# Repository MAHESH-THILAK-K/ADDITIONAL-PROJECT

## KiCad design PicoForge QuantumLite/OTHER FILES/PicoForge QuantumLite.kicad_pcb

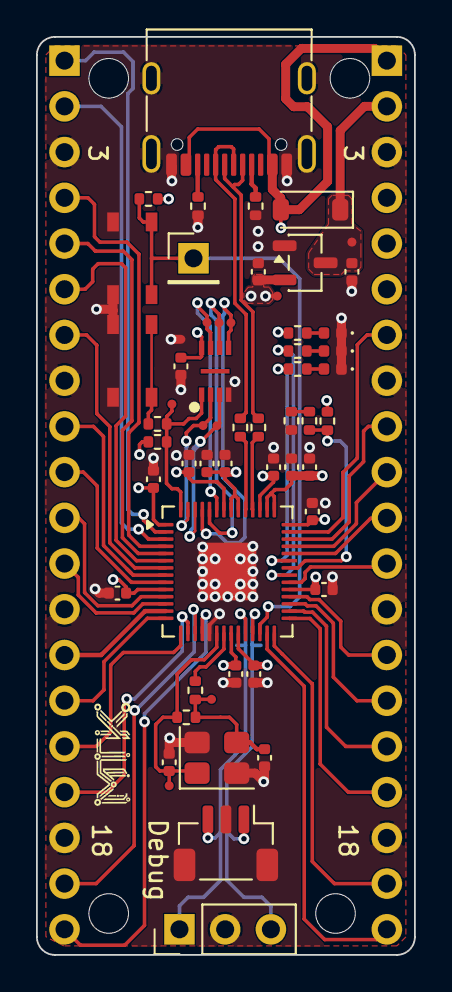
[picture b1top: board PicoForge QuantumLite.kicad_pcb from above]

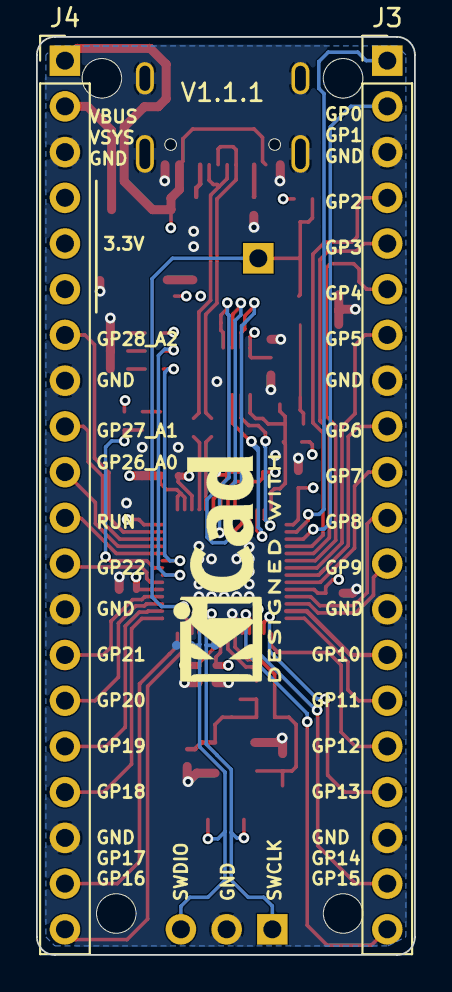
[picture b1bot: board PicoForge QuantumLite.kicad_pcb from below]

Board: 4 copper layers, 21.0 x 51.0 mm, 65 parts (5 on the bottom side), 58 nets.

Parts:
C1, C2, C5, C6, C7, C8, C9, C10, C11, C12, C15: 100nF; C_0402_1005Metric
C3, C4, C13, C14: 1uF; C_0402_1005Metric
C16, C17: 27p; C_0402_1005Metric
D1: D_Schottky; D_SOD-123
D2, D3, D4: LED; LED_0402_1005Metric
H1, H2, H3, H4: MountingHole; MountingHole_2.2mm_M2
J1: USB_C_Receptacle_USB2.0; USB_C_Receptacle_G-Switch_GT-USB-7010ASV
J3, J4: Conn_01x20; PinHeader_1x20_P2.54mm_Vertical
J5: Conn_01x03; PinHeader_1x03_P2.54mm_Vertical
J6: Conn_01x03_MountingPin; JST_SH_BM03B-SRSS-TB_1x03-1MP_P1.00mm_Vertical
J7: Conn_01x01_Pin; PinHeader_1x01_P2.54mm_Vertical
R1, R2, R3, R6, R7: 5.1k; R_0402_1005Metric
R4, R5: 27R; R_0402_1005Metric
R8, R9, R10, R11, R12, R13, R14, R15: 1k; R_0402_1005Metric
SW1, SW2: SW_Push; ALPSALPINE_SKRPACE010
TP1, TP2, TP3, TP4, TP5, TP6, TP7, TP8, TP9, TP10, TP11, TP12, TP13: TestPoint_pad
U1: XC6206P332MR; SOT-23-3
U2: RP2040; QFN-56-1EP_7x7mm_P0.4mm_EP3.2x3.2mm
U3: W25Q16JVUXIQ
Y1: 12MHz; Crystal_SMD_3225-4Pin_3.2x2.5mm

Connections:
+1V1: C1.1, C2.1, C3.1, U2.23 (DVDD), U2.45 (VREG_VOUT), U2.50 (DVDD)
+3.3V: C4.1, C5.1, C6.1, C7.1, C8.1, C9.1, C10.1, C11.1, C12.1, C14.1, C15.1, J4.4, J4.5, J4.6, R10.1, R11.1, R12.1, TP2.1 (1_1), U1.2 (VO), U2.1 (IOVDD), U2.10 (IOVDD), U2.22 (IOVDD), U2.33 (IOVDD), U2.42 (IOVDD), U2.43 (ADC_AVDD), U2.44 (VREG_IN), U2.48 (USB_VDD), U2.49 (IOVDD), U3.8 (VCC)
/CC1: J1.A5 (CC1), R1.1
/CC2: J1.B5 (CC2), R2.1
/GPIO0: J3.1, U2.2 (GPIO0)
/GPIO1: J3.2, U2.3 (GPIO1)
/GPIO2: J3.4, U2.4 (GPIO2)
/GPIO3: J3.5, U2.5 (GPIO3)
/GPIO4: J3.6, U2.6 (GPIO4)
/GPIO5: J3.7, U2.7 (GPIO5)
/GPIO6: J3.9, U2.8 (GPIO6)
/GPIO7: J3.10, U2.9 (GPIO7)
/GPIO8: J3.11, U2.11 (GPIO8)
/GPIO9: J3.12, U2.12 (GPIO9)
/GPIO10: J3.14, U2.13 (GPIO10)
/GPIO11: J3.15, U2.14 (GPIO11)
/GPIO12: J3.16, U2.15 (GPIO12)
/GPIO13: J3.17, U2.16 (GPIO13)
/GPIO14: J3.19, U2.17 (GPIO14)
/GPIO15: J3.20, U2.18 (GPIO15)
/GPIO16: J4.20, U2.27 (GPIO16)
/GPIO17: J4.19, U2.28 (GPIO17)
/GPIO18: J4.17, U2.29 (GPIO18)
/GPIO19: J4.16, U2.30 (GPIO19)
/GPIO20: J4.15, U2.31 (GPIO20)
/GPIO21: J4.14, U2.32 (GPIO21)
/GPIO22: J4.12, U2.34 (GPIO22)
/GPIO23: R13.1, U2.35 (GPIO23)
/GPIO24: R3.1, R6.2, U2.36 (GPIO24)
/GPIO25: R14.1, U2.37 (GPIO25)
/GPIO26_ADC0: J4.11, U2.38 (GPIO26_ADC0)
/GPIO27_ADC1: J4.10, U2.39 (GPIO27_ADC1)
/GPIO28_ADC2: J4.9, U2.40 (GPIO28_ADC2)
/GPIO29_ADC3: J4.7, U2.41 (GPIO29_ADC3)
/LED_3V3: D2.2 (A), R12.2
/LED_BUILT_IN1: D4.2 (A), R14.2
/LED_BUILT_IN2: D3.2 (A), R13.2
/QSPI_SCLK: TP9.1 (1_1), U2.52 (QSPI_SCLK), U3.6 (CLK)
/QSPI_SD0: TP10.1 (1_1), U2.53 (QSPI_SD0), U3.5 (DI(IO0))
/QSPI_SD1: TP11.1 (1_1), U2.55 (QSPI_SD1), U3.2 (DO(IO1))
/QSPI_SD2: TP12.1 (1_1), U2.54 (QSPI_SD2), U3.3 (IO2)
/QSPI_SD3: TP13.1 (1_1), U2.51 (QSPI_SD3), U3.7 (IO3)
/QSPI_SS: R10.2, R15.1, TP8.1 (1_1), U2.56 (QSPI_SS), U3.1 (~CS)
/RDIV: R6.1, R7.2
/RUN: J7.1 (Pin_1_1), R11.2, SW2.2, U2.26 (RUN)
/SW1_{PULL-UP}: R15.2, SW1.2
/SWCLK: J5.1, J6.3, TP5.1 (1_1), U2.24 (SWCLK)
/SWD: J5.3, J6.1, TP6.1 (1_1), U2.25 (SWD)
/USB_DN: J1.A7 (D-), J1.B7 (D-), R5.1
/USB_DP: J1.A6 (D+), J1.B6 (D+), R4.1
/USB_R_DN: R5.2, U2.46 (USB_DM)
/USB_R_DP: R4.2, U2.47 (USB_DP)
/Xin: C16.1, R8.1, TP3.1 (1_1), U2.20 (XIN), Y1.1
/Xout: R9.2, U2.21 (XOUT)
/XoutR: C17.1, R8.2, R9.1, TP4.1 (1_1), Y1.3
GND: C1.2, C2.2, C3.2, C4.2, C5.2, C6.2, C7.2, C8.2, C9.2, C10.2, C11.2, C12.2, C13.2, C14.2, C15.2, C16.2, C17.2, D2.1 (K), D3.1 (K), D4.1 (K), J1.A1 (GND), J1.A12 (GND), J1.B1 (GND), J1.B12 (GND), J1.SH (SHIELD), J3.3, J3.8, J3.13, J3.18, J4.3, J4.8, J4.13, J4.18, J5.2, J6.2, J6.MP (MountPin), R1.2, R2.2, R7.1, SW1.1, SW2.1, TP7.1 (1_1), U1.1 (GND), U2.19 (TESTEN), U2.57 (GND), U3.4 (GND), Y1.2, Y1.4
VBUS: D1.2 (A), J1.A4 (VBUS), J1.A9 (VBUS), J1.B4 (VBUS), J1.B9 (VBUS), J4.1, R3.2
VCC: C13.1, D1.1 (K), J4.2, TP1.1 (1_1), U1.3 (VI)

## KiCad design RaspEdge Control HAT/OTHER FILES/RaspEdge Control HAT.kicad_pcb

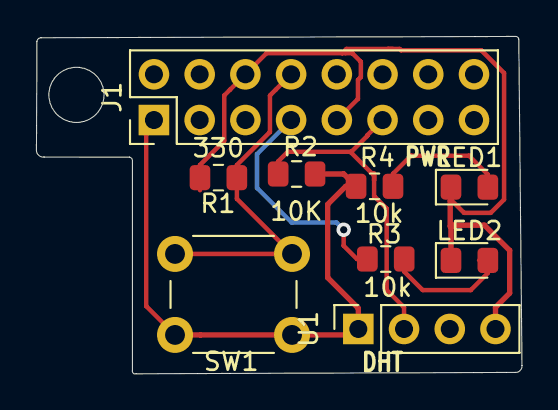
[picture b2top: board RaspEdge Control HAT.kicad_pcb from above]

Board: 2 copper layers, 27.0 x 18.7 mm, 9 parts (0 on the bottom side), 7 nets.

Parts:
J1: Raspberry_Pi_2_3; PinHeader_2x08_P2.54mm_Vertical
LED1, LED2: LED; LED_0805_2012Metric_Pad1.15x1.40mm_HandSolder
R1: 330; R_0805_2012Metric_Pad1.15x1.40mm_HandSolder
R2: 10K; R_0805_2012Metric_Pad1.15x1.40mm_HandSolder
R3, R4: 10k; R_0805_2012Metric_Pad1.15x1.40mm_HandSolder
SW1: SW_DPST; SW_PUSH_6mm_H8mm
U1: DHT22; PinSocket_1x04_P2.54mm_Vertical

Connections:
/3V3: J1.1, R2.2, R4.2, SW1.1, U1.1
/button_input: J1.8, R1.1, SW1.2
GND: J1.6, J1.9, LED1.1, LED2.1, R1.2, U1.4
unnamed: LED2.2, R3.1
unnamed: LED1.2, R4.1
unnamed: J1.7, R3.2
unnamed: J1.11, R2.1, U1.2

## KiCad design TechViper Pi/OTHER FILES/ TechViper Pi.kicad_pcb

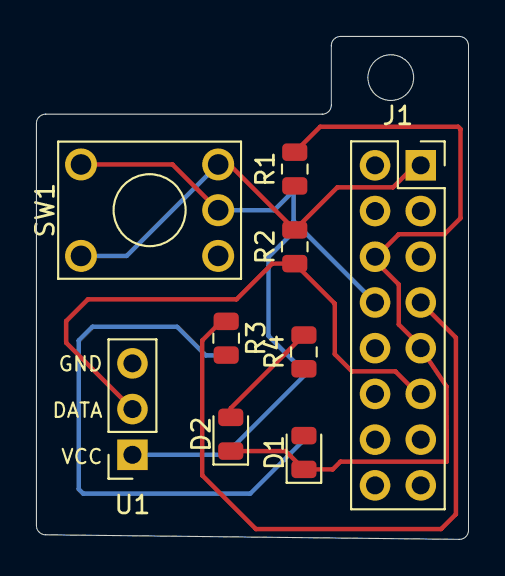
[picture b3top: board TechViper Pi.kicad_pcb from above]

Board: 2 copper layers, 24.0 x 27.9 mm, 9 parts (0 on the bottom side), 7 nets.

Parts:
D1, D2: LED; LED_0805_2012Metric
J1: Raspberry_Pi_2_3; PinSocket_2x08_P2.54mm_Vertical
R1: 10k; R_0805_2012Metric
R2: 330k; R_0805_2012Metric
R3, R4: R; R_0805_2012Metric
SW1: SW_DPST; KSA_Tactile_SPST
U1: DHT22; PinSocket_1x03_P2.54mm_Vertical

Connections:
/3V3: J1.1, R2.2, R4.1, SW1.1, SW1.3, U1.1
/button_input: J1.8, R1.1, SW1.2, SW1.4
GND: D1.1, D2.1, J1.6, J1.9, R1.2
unnamed: D1.2, R3.2
unnamed: D2.2, R4.2
unnamed: J1.7, R3.1
unnamed: J1.11, R2.1, U1.2

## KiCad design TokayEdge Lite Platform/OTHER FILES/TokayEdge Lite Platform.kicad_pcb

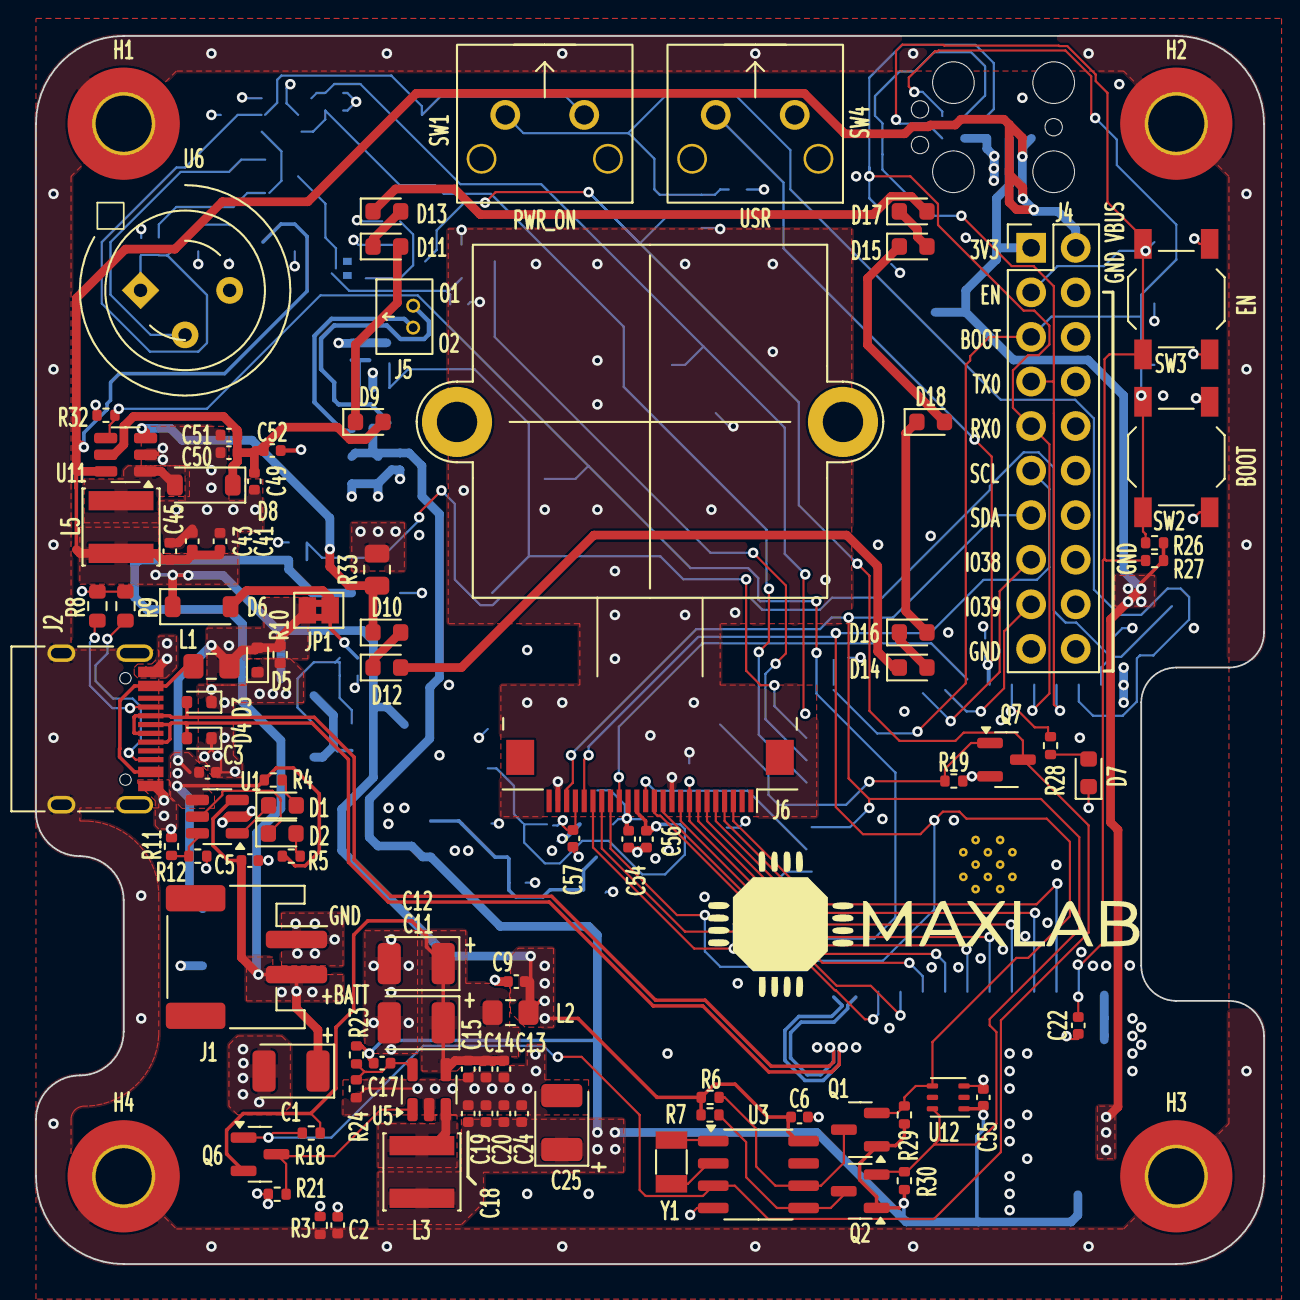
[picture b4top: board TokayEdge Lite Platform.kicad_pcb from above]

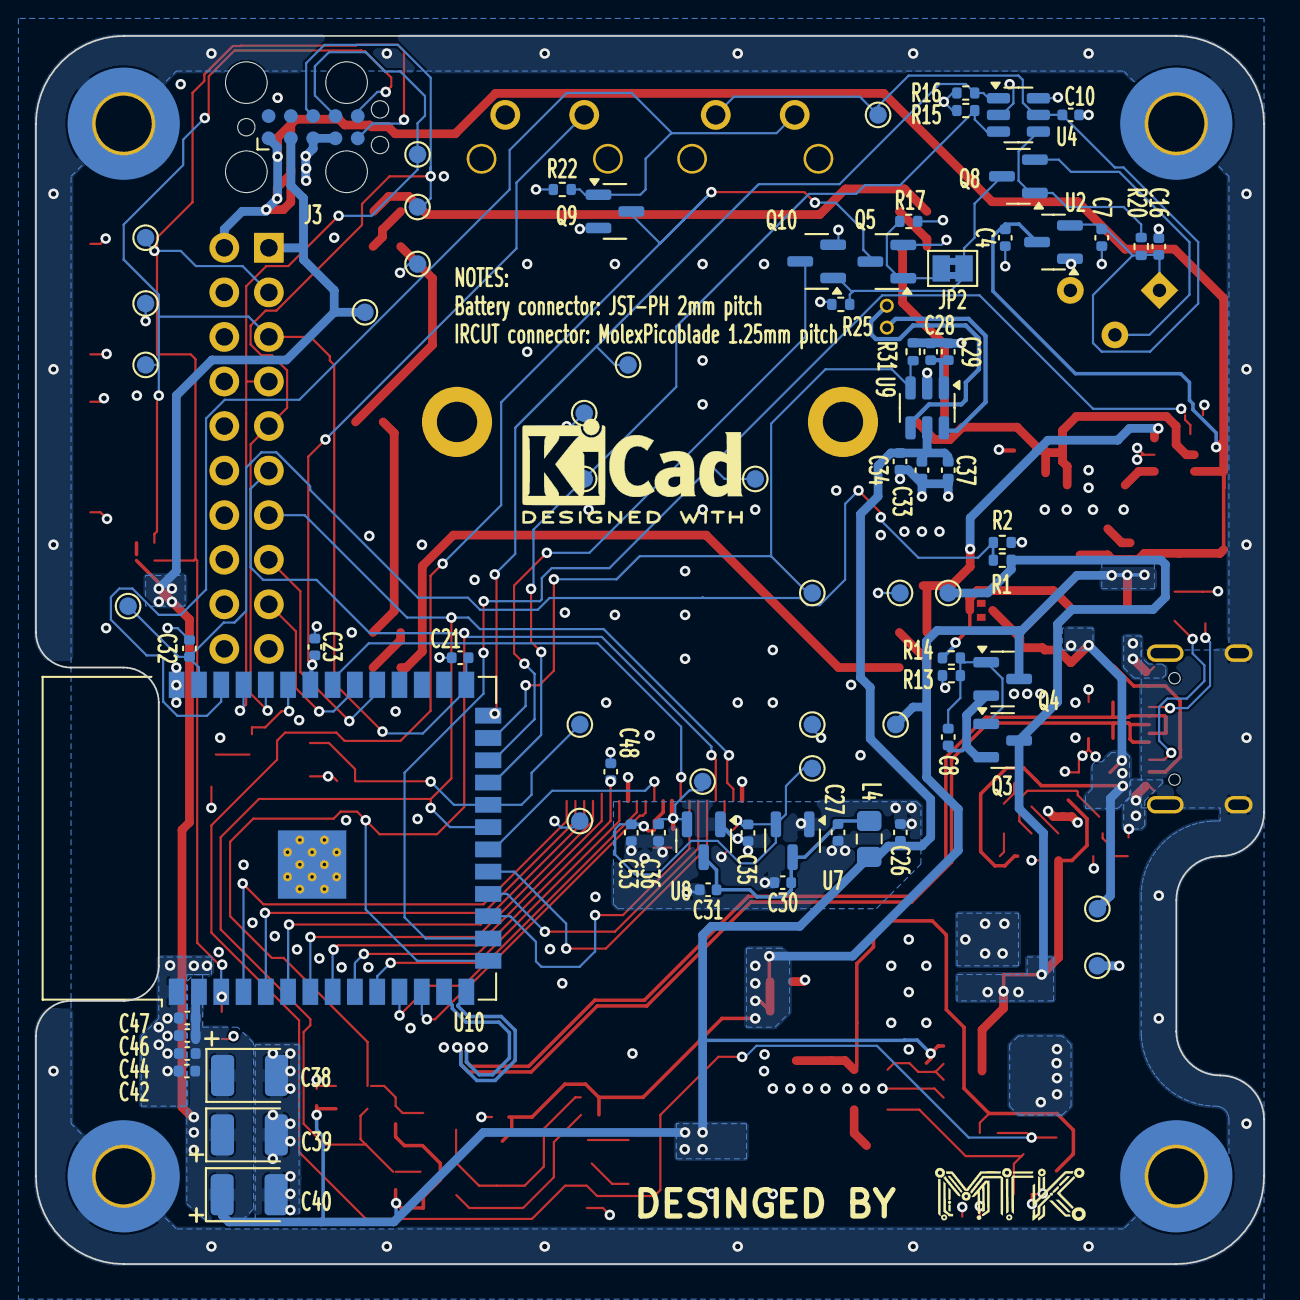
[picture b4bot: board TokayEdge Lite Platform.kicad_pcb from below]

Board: 4 copper layers, 70.0 x 70.0 mm, 176 parts (78 on the bottom side), 84 nets.

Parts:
C1, C11, C12, C25, C38, C39, C40: 100u_CASE-B-3528_TAJB107K006RNJ; CP_EIA-3528-15_AVX-H
C2, C3, C4, C5, C6, C7, C8, C9, C10, C13, C14, C15, C16, C18, C19, C20, C21, C22, C23, C24, C26, C27, C28, C29, C30, C31, C32, C33, C34, C35, C36, C37, C41, C42, C43, C44, C45, C46, C47, C49, C50, C51, C52, C53, C54, C55, C56, C57: 10u_0402_CL05A105KA5NQNC; C_0402_1005Metric
C17, C48: 22p_0402_0402CG220J500NT; C_0402_1005Metric
D1, D7: 0603_RED_KT-0603R; LED_0603_1608Metric
D2: 0603_GREEN_19-217/GHC-YR1S2/3T; LED_0603_1608Metric
D3, D4, D5: SOD-523_BSD5C051L; D_SOD-523
D6, D8: B5819W-SL_SOD-123; D_SOD-123
D9, D10, D11, D12, D13, D14, D15, D16, D17, D18: 0603_IR_850nm_E6C0603IRAC1UDA; LED_0603_1608Metric
H1, H2, H3, H4: MountingHole_Pad; MountingHole_3.2mm_M3_Pad_TopBottom
J1: Conn-01x02_P2mm_NONAME_JST-PH_C47647; JST_PH_S2B-PH-SM4-TB_1x02-1MP_P2.00mm_Horizontal
J2: TYPE-C-31-M-12; USB_C_Receptacle_HRO_TYPE-C-31-M-12
J3: MAXLAB; Tag-Connect_TC2050-IDC-FP_2x05_P1.27mm_Vertical
J4: Conn-02x10_P2.54mm_B-2100S20P-B110; PinHeader_2x10_P2.54mm_Vertical
J5: Conn-01x02_P1.25mm_10114829-10102LF; 10114829-10102LF
J6: Conn_01x24_FFC_0.5mm_AFC01-S24FCC-00; Jushuo_AFC01-S24FCC-00_1x24-1MP_P0.50_Horizontal
JP1: USB_PWR; SolderJumper-2_P1.3mm_Bridged2Bar_Pad1.0x1.5mm
JP2: PIR; SolderJumper-2_P1.3mm_Bridged2Bar_Pad1.0x1.5mm
L1, L2, L4: FB_2A_0805_220R@100MHz_BLM21PG221SN1D; L_0805_2012Metric_Pad1.15x1.40mm_HandSolder
L3, L5: 10u_1.5A_4x4mm_SWPA4030S100MT; L_Sunlord_SWPA40xxS
Q1, Q2, Q5, Q7, Q9, Q10: 2N7002; SOT-23
Q3, Q4, Q6, Q8: AO3401A; SOT-23
R1, R2, R23: 976k_0402_0402WGD9763TCE; R_0402_1005Metric
R3, R13, R15, R16, R17, R18, R19, R21, R22, R24, R25, R31, R32: 215k_0402_0402WGD2153TCE; R_0402_1005Metric
R4, R5, R28: 1k_0402_0402WGF1001TCE; R_0402_1005Metric
R6, R7, R10, R11, R12, R14, R20, R26, R27, R29, R30: 10k_0402_0402WGF1002TCE; R_0402_1005Metric
R8, R9: 5.1k_0603_0603WAF5101T5E; R_0603_1608Metric
R33: 2.43R_0805_0805W8F243KT5E; R_0805_2012Metric
SW1, SW4: SW_PB_90deg_K2-1102AQ-H4CW-01
SW2, SW3: SW_PB_TS-1187A-B-A-B; SW_SPST_TL3342
TP1, TP2, TP3, TP4, TP5, TP6, TP7, TP8, TP9, TP10, TP11, TP12, TP13, TP14, TP15, TP16, TP17, TP18, TP19, TP20, TP21, TP22, TP23, TP24: TestPoint; TestPoint_Pad_D1.0mm
U1: TP4057-42-SOT26-R; SOT-23-6
U2, U7: XC6206-2.8V; SOT-23
U3: PCF85063AT; SO-8_3.9x4.9mm_P1.27mm
U4: TI_SN74LVC1G373DBVR; SOT-23-6
U5: SY8089AAAC; SOT-23-5
U6: PIR_AS312; AS312
U8: RT9166-12GVL; SOT-23
U9: AP1511B; SOT-23-6
U10: ESP32-S3-WROOM-1-N16R8; ESP32-S3-WROOM-1
U11: MT9284-28J; SOT-23-6
U12: LTR-303ALS-01; Lite-On_LTR-303ALS-01
Y1: 32.768kHz_Q13FC1350000400; Crystal_SMD_3215-2Pin_3.2x1.5mm

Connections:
+1V2: C36.1, C54.2, J6.15, TP16.1, U8.2 (VO)
+2V8: C35.1, C53.1, C56.2, C57.2, J6.14, J6.21, TP18.1, U7.2 (VO)
+3V3: C17.1, C18.2, C19.2, C20.2, C24.2, C25.1, C26.1, C33.2, C34.2, C37.2, C38.1, C39.1, C40.1, C42.1, C44.1, C46.1, C47.1, C55.1, J3.2, J4.1, L3.2, L4.1, Q1.1 (G), Q2.1 (G), R23.1, R26.2, R27.2, R29.1, R30.1, TP22.1, U9.5 (VDD), U10.2 (3V3), U12.1 (VDD)
+5V: C3.2, D5.2 (A2), JP1.2 (B), L1.2, R4.1, R5.1, R10.1, TP23.1, U1.4 (V_{cc})
+BATT: C1.1, C5.1, J1.2, Q3.3 (D), R1.1, TP19.1, U1.3 (BAT)
/BATT_DETECT: C32.1, R1.2, R2.1, TP11.1, U10.39 (GPIO1/TOUCH1/ADC1_CH0)
/CAM.D2: J6.6, U10.7 (GPIO7/TOUCH7/ADC1_CH6)
/CAM.D3: J6.4, U10.5 (GPIO5/TOUCH5/ADC1_CH4)
/CAM.D4: J6.3, U10.4 (GPIO4/TOUCH4/ADC1_CH3)
/CAM.D5: J6.5, U10.6 (GPIO6/TOUCH6/ADC1_CH5)
/CAM.D6: J6.7, U10.8 (GPIO15/U0RTS/ADC2_CH4/XTAL_32K_P)
/CAM.D7: J6.9, U10.10 (GPIO17/U1TXD/ADC2_CH6)
/CAM.D8: J6.11, U10.11 (GPIO18/U1RXD/ADC2_CH7/CLK_OUT3)
/CAM.D9: J6.13, U10.20 (GPIO12/TOUCH12/ADC2_CH1/FSPICLK/FSPIIO6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)
/CAM.HREF: J6.16, U10.33 (MTDO/GPIO40/CLK_OUT2)
/CAM.MCLK: J6.12, U10.12 (GPIO8/TOUCH8/ADC1_CH7/SUBSPICS1)
/CAM.PCLK: C48.1, J6.8, U10.9 (GPIO16/U0CTS/ADC2_CH5/XTAL_32K_NH5)
/CAM.PWDN: J6.17, U10.17 (GPIO9/TOUCH9/ADC1_CH8/FSPIHD/SUBSPIHD)
/CAM.RST: J6.19, U10.19 (GPIO11/TOUCH11/ADC2_CH0/FSPID/FSPIIO5/S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)
/CAM.SCL: J4.11, J6.20, Q1.2 (S), R29.2, U10.15 (GPIO3/TOUCH3/ADC1_CH2), U12.4 (SCL)
/CAM.SDA: J4.13, J6.22, Q2.2 (S), R30.2, U10.21 (GPIO13/TOUCH13/ADC2_CH2/FSPIQ/FSPIIO7/S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), U12.6 (SDA)
/CAM.VSYNC: J6.18, U10.18 (GPIO10/TOUCH10/ADC1_CH9/FSPICS0/FSPIIO4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)
/ESP_BOOT: C21.2, J3.6, J4.5, R26.1, SW2.2, TP2.1, U10.27 (GPIO0/BOOT)
/ESP_EN: C22.2, J3.5, J4.3, R27.1, SW3.2, TP1.1, U10.3 (EN)
/IO38: J4.15, U10.31 (GPIO38/FSPIWP/SUBSPIWP)
/IO39: J4.17, U10.32 (MTCK/GPIO39/CLK_OUT3/SUBSPICS1)
/IRCUT_CTRL: R31.2, TP10.1, U9.3 (FBC), U10.25 (GPIO48/SPICLK_N/SUBSPICLK_N_DIFF)
/IRLED_PWM: R32.2, TP14.1, U10.16 (GPIO46), U11.4 (EN)
/PIR_CTRL_D: R15.2, TP8.1, U4.3 (D), U10.23 (GPIO21)
/PIR_CTRL_LE: R16.2, TP7.1, U4.1 (LE), U10.26 (GPIO45)
/PIR_OUT: Q10.3 (D), U10.24 (GPIO47/SPICLK_P/SUBSPICLK_P_DIFF)
/PWRON_DET: Q9.1 (G), R22.2, SW1.2, U10.38 (GPIO2/TOUCH2/ADC1_CH1)
/PWR_EN: Q7.1 (G), R19.2, TP12.1, U10.22 (GPIO14/TOUCH14/ADC2_CH3/FSPIWP/FSPIDQS/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)
/PWR_PIR: C7.1, C10.1, C16.1, R20.1, SW1.1, TP13.1, U2.2 (VO), U4.5 (VCC), U6.1 (VDD)
/RXD0: J3.8, J4.9, TP5.1, U10.36 (U0RXD/GPIO44/CLK_OUT2)
/TXD0: J3.7, J4.7, TP4.1, U10.37 (U0TXD/GPIO43/CLK_OUT1)
/UD+: D4.2 (A2), J2.A6 (D+), J2.B6 (D+), U10.14 (GPIO20/U1CTS/ADC2_CH9/CLK_OUT1/USB_D+)
/UD-: D3.2 (A2), J2.A7 (D-), J2.B7 (D-), U10.13 (GPIO19/U1RTS/ADC2_CH8/CLK_OUT2/USB_D-)
/USR_BTN: C23.2, SW4.2, U10.34 (MTDI/GPIO41/CLK_OUT1)
/USR_LED: R28.1, U10.35 (MTMS/GPIO42)
GND: C1.2, C2.1, C3.1, C4.1, C5.2, C6.2, C7.2, C9.1, C10.2, C11.2, C12.2, C13.1, C14.2, C15.1, C16.2, C18.1, C19.1, C20.1, C21.1, C22.1, C23.1, C24.1, C25.2, C26.2, C27.2, C28.2, C29.2, C30.2, C31.2, C32.2, C33.1, C34.1, C35.2, C36.2, C37.1, C38.2, C39.2, C40.2, C41.1, C42.2, C43.2, C44.2, C45.1, C46.2, C47.2, C48.2, C49.2, C50.1, C51.1, C52.1, C53.2, C54.1, C55.2, C56.1, C57.1, D3.1 (A1), D4.1 (A1), D5.1 (A1), D7.1 (K), J1.1, J2.A1 (GND), J2.A12 (GND), J2.B1 (GND), J2.B12 (GND), J3.3, J3.4, J4.4, J4.6, J4.8, J4.10, J4.12, J4.14, J4.16, J4.18, J4.19, J4.20, J6.10, J6.23, Q5.2 (S), Q7.2 (S), Q9.2 (S), Q10.2 (S), R2.2, R3.2, R8.2, R9.2, R10.2, R11.2, R12.2, R13.2, R15.1, R16.1, R17.1, R19.1, R21.2, R22.1, R24.2, R25.1, R31.1, R32.1, R33.2, SW2.1, SW3.1, SW4.1, TP3.1, TP6.1, TP9.1, TP15.1, TP17.1, TP20.1, TP24.1, U1.2 (GND), U2.1 (GND), U3.4 (VSS), U4.2 (G), U4.6 (~OE), U5.2 (GND), U6.3 (VSS), U7.1 (GND), U8.1 (GND), U9.2 (GND), U10.1 (GND), U10.40 (GND), U10.41 (GND), U11.2 (GND), U12.3 (GND)
GNDPWR: C2.2, H1.1, H2.1, H3.1, H4.1, J2.S1 (SHIELD), R3.1
unnamed: D1.2 (A), R4.2
unnamed: D1.1 (K), U1.1 (~CHRG)
unnamed: D2.2 (A), R5.2
unnamed: D2.1 (K), U1.5 (~STDBY)
unnamed: D6.2 (A), JP1.1 (A), R14.1
unnamed: D7.2 (A), R28.2
unnamed: D8.2 (A), L5.2, U11.1 (SW)
unnamed: C49.1, C50.2, C51.2, C52.2, D8.1 (K), D9.2 (A), U11.5 (OV)
unnamed: D10.2 (A), D12.1 (K)
unnamed: D10.1 (K), R33.1, U11.3 (FB)
unnamed: D9.1 (K), D11.2 (A)
unnamed: D11.1 (K), D13.2 (A)
unnamed: D12.2 (A), D14.1 (K)
unnamed: D13.1 (K), D15.2 (A)
unnamed: D14.2 (A), D16.1 (K)
unnamed: D15.1 (K), D17.2 (A)
unnamed: D16.2 (A), D18.1 (K)
unnamed: D17.1 (K), D18.2 (A)
unnamed: J2.A5 (CC1), R8.1
unnamed: J2.B5 (CC2), R9.1
unnamed: J2.A4 (VBUS), J2.A9 (VBUS), J2.B4 (VBUS), J2.B9 (VBUS), L1.1
unnamed: J5.1, U9.6 (OUT2)
unnamed: J5.2, U9.4 (OUT1)
unnamed: JP2.1 (A), Q8.3 (D), Q10.1 (G), R25.2
unnamed: JP2.2 (B), Q5.1 (G), R17.2
unnamed: Q1.3 (D), R6.2, U3.6 (SCL)
unnamed: Q2.3 (D), R7.2, U3.5 (SDA)
unnamed: C8.1, Q3.1 (G), Q4.1 (G), R13.1, R14.2
unnamed: C8.2, Q3.2 (S), Q4.2 (S)
unnamed: Q5.3 (D), Q6.1 (G), Q7.3 (D), Q9.3 (D), R18.2, U3.3 (~INT)
unnamed: Q6.3 (D), R21.1, U5.1 (EN)
unnamed: C11.1, C12.1, C13.2, C14.1, C15.2, L2.2, Q6.2 (S), R18.1, U5.4 (IN)
unnamed: Q8.1 (G), R20.2, U4.4 (Q)
unnamed: Q8.2 (S), U6.2 (REL)
unnamed: R11.1, R12.1, U1.6 (PROG)
unnamed: U3.1 (OSCI), Y1.2
unnamed: U3.2 (OSCO), Y1.1
unnamed: C17.2, R23.2, R24.1, U5.5 (FB)
unnamed: L3.1, U5.3 (LX)
unnamed: C27.1, C30.1, C31.1, L4.2, U7.3 (VI), U8.3 (VI)
unnamed: C28.1, C29.1, U9.1 (CE)
VBUS: C4.2, C6.1, C9.2, C41.2, C43.1, C45.2, D6.1 (K), J3.1, J4.2, L2.1, L5.1, Q4.3 (D), R6.1, R7.1, TP21.1, U2.3 (VI), U3.8 (VDD), U11.6 (VIN)

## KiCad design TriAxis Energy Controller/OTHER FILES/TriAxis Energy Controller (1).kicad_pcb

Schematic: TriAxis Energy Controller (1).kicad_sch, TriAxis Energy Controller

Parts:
BT1: Battery; BatteryHolder_Keystone_2462_2xAA
C1, C2, C3, C4, C5, C6, C8, C9, C10, C11, C12, C16: 2A103J; C_Disc_D9.0mm_W5.0mm_P5.00mm
C7: 2A103J; C_Disc_D8.0mm_W2.5mm_P5.00mm
C13, C17: 2A103J; C_Disc_D11.0mm_W5.0mm_P5.00mm
C14: 2A103; C_Disc_D11.0mm_W5.0mm_P7.50mm
C15: 2A103J; C_Disc_D11.0mm_W5.0mm_P7.50mm
C18: 103; C_Disc_D11.0mm_W5.0mm_P5.00mm
C19, C20: C; C_Disc_D11.0mm_W5.0mm_P5.00mm
D1, D2, D3, D4, D5, D6, D7, D8, D9, D10, D11, D12: 1N4007; D_DO-41_SOD81_P7.62mm_Horizontal
D13, D14, D15: 1N47xxA; D_DO-35_SOD27_P7.62mm_Horizontal
D16, D18: LED; LED_Rectangular_W3.9mm_H1.9mm
D17: LED; LED_Rectangular_W3.9mm_H1.8mm
D19, D20, D21: 1N4007; D_DO-41_SOD81_P10.16mm_Horizontal
J1: Screw_Terminal_01x04; TerminalBlock_Altech_AK300-4_P5.00mm
J2: Jack-DC; BarrelJack_CUI_PJ-063AH_Horizontal
J3: Conn_01x04_Male; FanPinHeader_1x04_P2.54mm_Vertical
R1, R5, R9: 1M; R_Axial_DIN0207_L6.3mm_D2.5mm_P7.62mm_Horizontal
R2, R6, R10: 100K; R_Axial_DIN0207_L6.3mm_D2.5mm_P7.62mm_Horizontal
R3, R7, R11, R13, R14, R15: 10K; R_Axial_DIN0207_L6.3mm_D2.5mm_P7.62mm_Horizontal
R4, R8, R12: 2.2K; R_Axial_DIN0207_L6.3mm_D2.5mm_P7.62mm_Horizontal
R16, R17, R21: 47k; R_Axial_DIN0207_L6.3mm_D2.5mm_P7.62mm_Horizontal
R18, R19, R20: 20k; R_Axial_DIN0207_L6.3mm_D2.5mm_P7.62mm_Horizontal
R22, R23, R24: 57k; R_Axial_DIN0207_L6.3mm_D2.5mm_P7.62mm_Horizontal
U1, U2, U3: LM3578; DIP-8_W7.62mm_Socket_LongPads
U4: L7809; 3-SIP_Module_V7805-500
U5: ATmega328-PU; DIP-28_W7.62mm_Socket
Y1: Crystal; Crystal_HC49-U_Vertical

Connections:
/A0: D13.1 (K), J3.2, R16.1, U1.1 (E-), U5.14
/A1: D15.1 (K), J3.3, R21.1, U2.1 (E-), U5.15
/A2: D14.1 (K), J3.4, R17.1, U3.1 (E-), U5.16
/DC_IN: J2.2, U4.1 (IN)
/GND: BT1.2 (-), C1.2, C2.2, C3.2, C4.2, C5.2, C6.2, C7.2, C8.2, C9.2, C10.2, C11.2, C12.2, C13.1, C14.1, C15.1, C16.1, C17.1, C18.1, D1.2 (A), D2.2 (A), D5.2 (A), D6.2 (A), D9.2 (A), D10.2 (A), D13.2 (A), D14.2 (A), D15.2 (A), J2.1, J3.1, R4.2, R8.2, R12.2, R18.2, R19.2, R20.2, U1.4 (GND), U2.4 (GND), U3.4 (GND), U4.2 (GND), U5.8, U5.22
/L1: D1.1 (K), D3.2 (A), J1.4, R22.2
/L2: D5.1 (K), D7.2 (A), J1.3, R23.2
/L3: D9.1 (K), D11.2 (A), J1.2, R24.2
/N: D2.1 (K), D4.2 (A), D6.1 (K), D8.2 (A), D10.1 (K), D12.2 (A), D19.1 (K), D20.1 (K), D21.1 (K), J1.1
/P5U1: C10.1, C16.2, R13.1, U1.5 (E)
/P5U2: C11.1, C17.2, R14.1, U2.5 (E)
/P5U3: C12.1, C18.2, R15.1, U3.5 (E)
/SG1: C1.1, D3.1 (K), D4.1 (K), R1.1
/SG2: C2.1, D7.1 (K), D8.1 (K), R5.1
/SG3: C3.1, D11.1 (K), D12.1 (K), R9.1
/VCC: BT1.1 (+), C13.2, C14.2, C15.2, U1.8 (VIN), U2.8 (VIN), U3.8 (VIN), U4.3 (OUT), U5.7, U5.20
unnamed: C4.1, C8.1, R3.2, R4.1, R13.2
unnamed: C5.1, C7.1, R7.2, R8.1, R14.2
unnamed: C6.1, C9.1, R11.2, R12.1, R15.2
unnamed: C19.1, C20.1
unnamed: C19.2, U5.9, Y1.2
unnamed: C20.2, U5.10, Y1.1
unnamed: D16.1 (K), D19.2 (A)
unnamed: D16.2 (A), R22.1
unnamed: D17.1 (K), D20.2 (A)
unnamed: D17.2 (A), R23.1
unnamed: D18.1 (K), D21.2 (A)
unnamed: D18.2 (A), R24.1
unnamed: R1.2, R2.1
unnamed: R2.2, R3.1
unnamed: R5.2, R6.1
unnamed: R6.2, R7.1
unnamed: R9.2, R10.1
unnamed: R10.2, R11.1
unnamed: R16.2, R18.1, U1.2 (E+)
unnamed: R17.2, R20.1, U3.2 (E+)
unnamed: R19.1, R21.2, U2.2 (E+)
unnamed: U1.3 (CAP), U1.6 (C), U1.7 (ILIM)
unnamed: U2.3 (CAP), U2.6 (C), U2.7 (ILIM)
unnamed: U3.3 (CAP), U3.6 (C), U3.7 (ILIM)

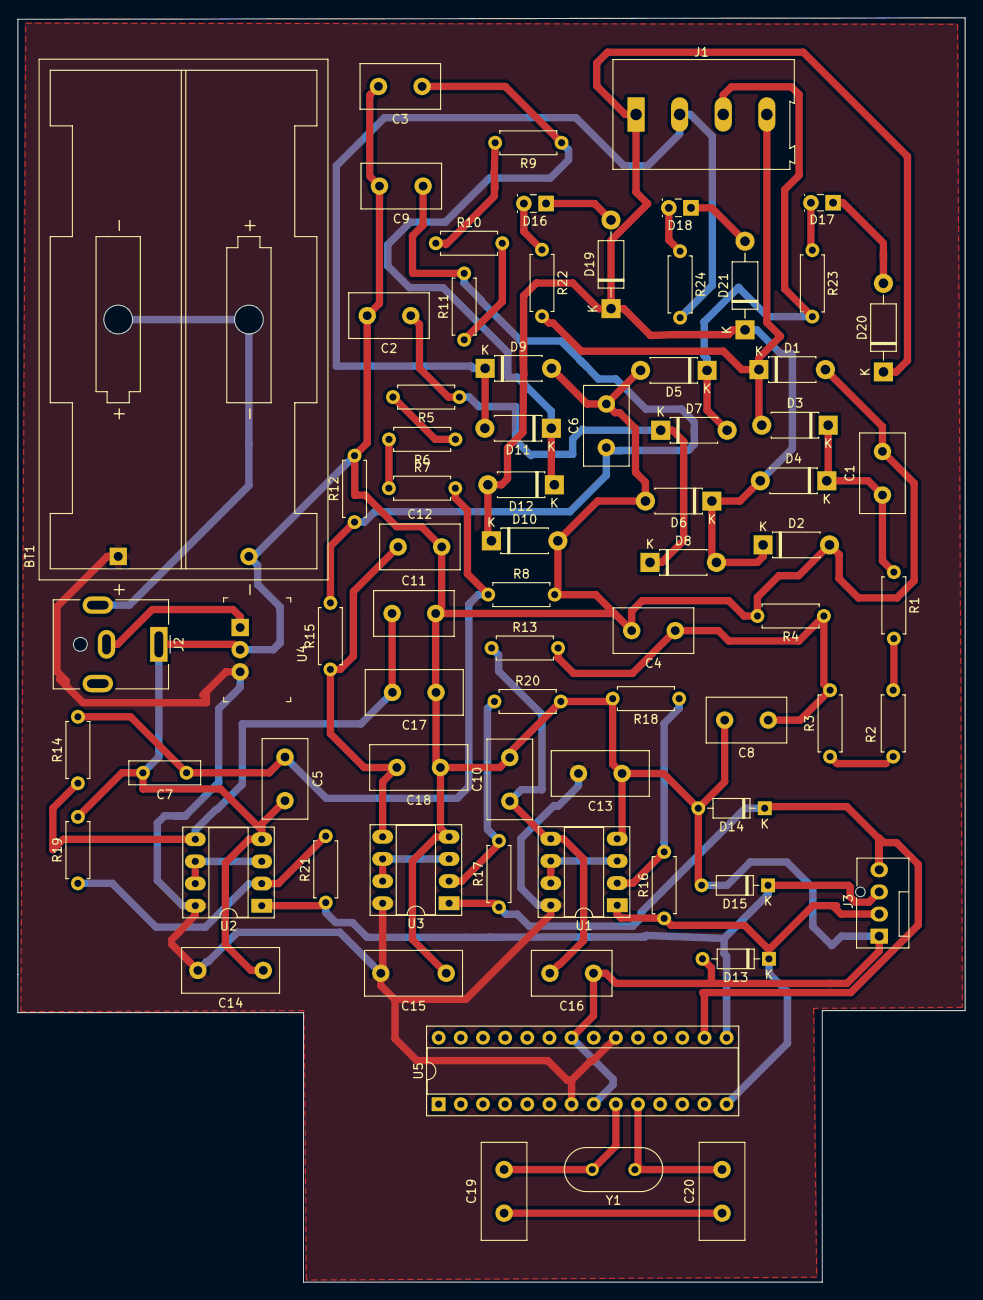
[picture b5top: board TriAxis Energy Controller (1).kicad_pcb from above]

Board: 2 copper layers, 108.6 x 145.0 mm, 75 parts (0 on the bottom side), 40 nets.
